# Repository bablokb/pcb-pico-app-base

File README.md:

Generic application base PCB for the Raspberry Pi Pico(W)
=========================================================

**This is work in progress**

A generic application base PCB for the Pi Pico(W) and compatible
development boards.

Core features:

  - RTC (PCF8563)
  - integrated power-management with
    - near zero power-off current
    - time-based wake up via RTC-alarm
    - wake up via interrupt (e.g. with a button)
    - JST-PH2 LiPo connector
    - LiPo charging
    - battery fuel-gauge
  - I2C connectors (Stemma/Qt and Grove)
  - EYESPI connector
  - integrated XTSD-chip for data-storage
  - additional THT for all GPIOs
  - multiple 3V3+GND connectors

License
-------

[![CC BY-SA 4.0][cc-by-sa-shield]][cc-by-sa]

This work is licensed under a
[Creative Commons Attribution-ShareAlike 4.0 International
License][cc-by-sa].

[![CC BY-SA 4.0][cc-by-sa-image]][cc-by-sa]

[cc-by-sa]: http://creativecommons.org/licenses/by-sa/4.0/
[cc-by-sa-image]: https://licensebuttons.net/l/by-sa/4.0/88x31.png
[cc-by-sa-shield]:
https://img.shields.io/badge/License-CC%20BY--SA%204.0-lightgrey.svg

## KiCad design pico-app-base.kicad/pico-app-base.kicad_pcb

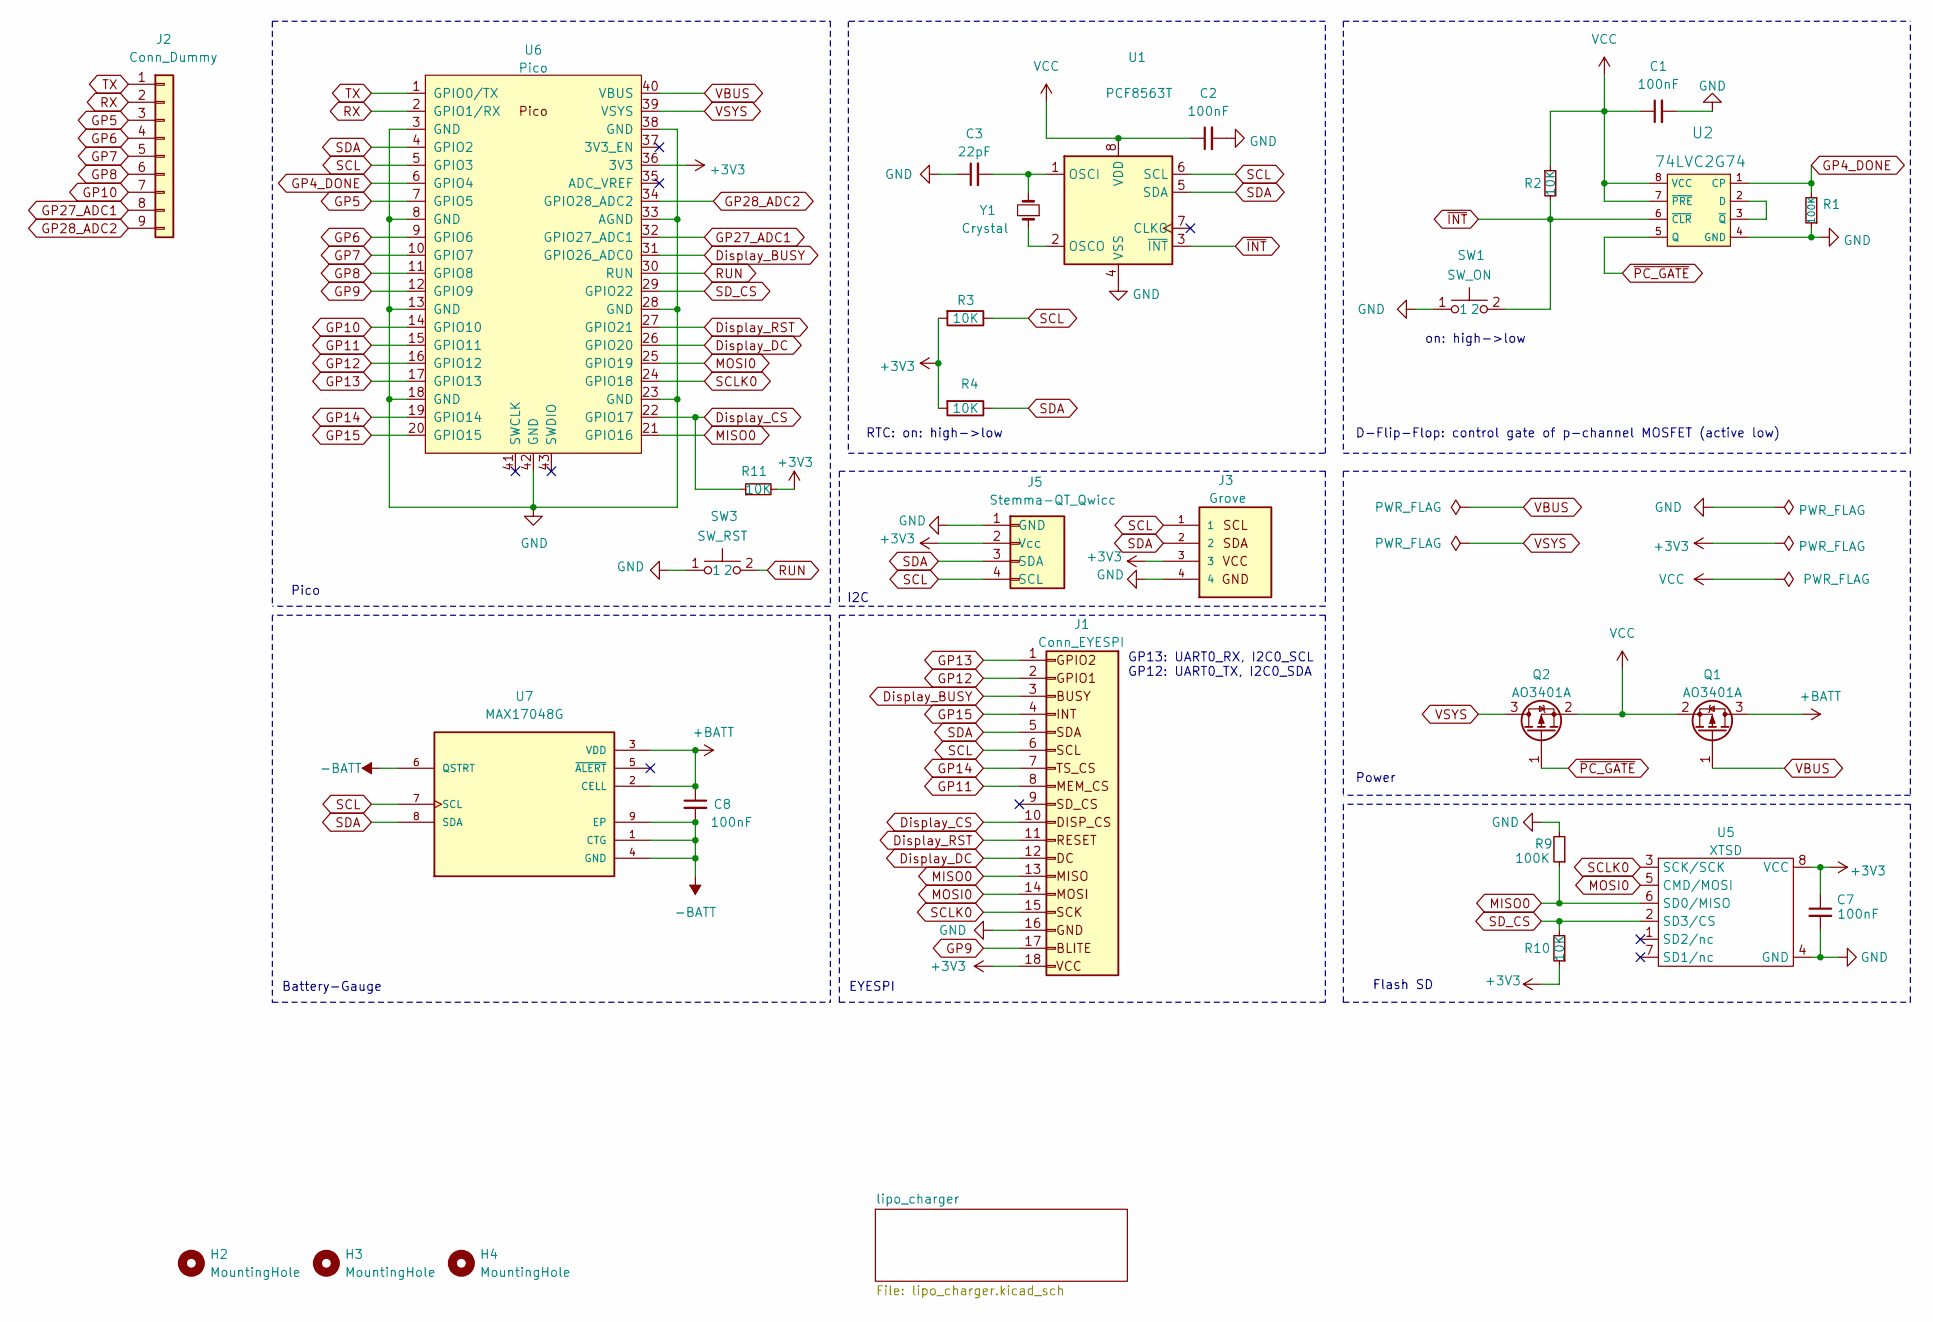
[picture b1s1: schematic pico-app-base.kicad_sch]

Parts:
C1, C2, C7, C8: 100nF; C_0402_1005Metric; LCSC C1525
C3: 22pF; C_0402_1005Metric; LCSC C1555
H2, H3, H4: MountingHole; MountingHole_2.5mm
J1: Conn_EYESPI; G-Shell-FPC_1x18_P0.50mm_Horizontal; LCSC C21260844
J2: Conn_Dummy
J3: Grove; grove_vertical
J5: Stemma-QT_Qwicc; JST_SH_SM04B-SRSS-TB_1x04-1MP_P1.00mm_Horizontal; LCSC C160404
Q1, Q2: AO3401A; SOT-23; LCSC C15127
R1, R9: 100K; R_0402_1005Metric; LCSC C25741
R2, R3, R4, R10, R11: 10K; R_0402_1005Metric; LCSC C25744
SW1: SW_ON; SW_PUSH_1x_6mm
SW3: SW_RST; SW_PUSH_1x_6mm
U1: PCF8563T; SOIC-8_3.9x4.9mm_P1.27mm; LCSC C7440
U2: 74LVC2G74; TSSOP-8_3x3mm_P0.65mm; MPN SN74HC74N; Digi-Key_PN 296-1602-5-ND
U5: XTSD; LGA8_8X6; LCSC C558837
U6: Pico; RPi_Pico_SMD_TH_extended
U7: MAX17048G; LCSC C2682616
Y1: Crystal; Crystal_SMD_3215-2Pin_3.2x1.5mm; LCSC C32346

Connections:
+3V3: C7.1, J1.18, J3.3, J5.2 (Vcc), R3.2, R4.2, R10.1, R11.2, U5.8 (VCC), U6.36 (3V3)
+BATT: C8.1, Q1.3 (D), U7.2 (CELL), U7.3 (VDD); also elsewhere on the board
-BATT: C8.2, U7.1 (CTG), U7.4 (GND), U7.6 (QSTRT), U7.9 (EP); also elsewhere on the board
Display_BUSY: J1.3, U6.31 (GPIO26_ADC0)
Display_CS: J1.10, R11.1, U6.22 (GPIO17)
Display_DC: J1.12, U6.26 (GPIO20)
Display_RST: J1.11, U6.27 (GPIO21)
GND: C1.2, C2.2, C3.1, C7.2, J1.16, J3.4, J5.1 (GND), R1.1, R9.2, SW1.1, SW3.1, U1.4 (VSS), U2.4 (GND), U5.4 (GND), U6.3 (GND), U6.8 (GND), U6.13 (GND), U6.18 (GND), U6.23 (GND), U6.28 (GND), U6.33 (AGND), U6.38 (GND), U6.42 (GND); also elsewhere on the board
GP4_DONE: R1.2, U2.1 (CP), U6.6 (GPIO4)
GP5: J2.3, U6.7 (GPIO5)
GP6: J2.4, U6.9 (GPIO6)
GP7: J2.5, U6.10 (GPIO7)
GP8: J2.6, U6.11 (GPIO8)
GP9: J1.17, U6.12 (GPIO9)
GP10: J2.7, U6.14 (GPIO10)
GP11: J1.8, U6.15 (GPIO11)
GP12: J1.2, U6.16 (GPIO12)
GP13: J1.1, U6.17 (GPIO13)
GP14: J1.7, U6.19 (GPIO14)
GP15: J1.4, U6.20 (GPIO15)
GP27_ADC1: J2.8, U6.32 (GPIO27_ADC1)
GP28_ADC2: J2.9, U6.34 (GPIO28_ADC2)
MISO0: J1.13, R9.1, U5.6 (SD0/MISO), U6.21 (GPIO16)
MOSI0: J1.14, U5.5 (CMD/MOSI), U6.25 (GPIO19)
unnamed: C3.2, U1.1 (OSCI), Y1.2
unnamed: U1.2 (OSCO), Y1.1
unnamed: U2.2 (D), U2.3 (~Q)
RUN: SW3.2, U6.30 (RUN)
RX: J2.2, U6.2 (GPIO1/RX)
SCL: J1.6, J3.1, J5.4 (SCL), R3.1, U1.6 (SCL), U6.5 (GPIO3), U7.7 (SCL)
SCLK0: J1.15, U5.3 (SCK/SCK), U6.24 (GPIO18)
SDA: J1.5, J3.2, J5.3 (SDA), R4.1, U1.5 (SDA), U6.4 (GPIO2), U7.8 (SDA)
SD_CS: R10.2, U5.2 (SD3/CS), U6.29 (GPIO22)
TX: J2.1, U6.1 (GPIO0/TX)
VBUS: Q1.1 (G), U6.40 (VBUS); also elsewhere on the board
VCC: C1.1, C2.1, Q1.2 (S), Q2.2 (S), R2.1, U1.8 (VDD), U2.7 (~PRE), U2.8 (VCC)
VSYS: Q2.3 (D), U6.39 (VSYS)
~INT: R2.2, SW1.2, U1.3 (~INT), U2.6 (~CLR)
~PC_GATE: Q2.1 (G), U2.5 (Q)

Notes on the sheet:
Battery-Gauge
EYESPI
Power
Flash SD
D-Flip-Flop: control gate of p-channel MOSFET (active low)
Pico
RTC: on: high->low
I2C
on: high->low
GP13: UART0_RX, I2C0_SCL GP12: UART0_TX, I2C0_SDA

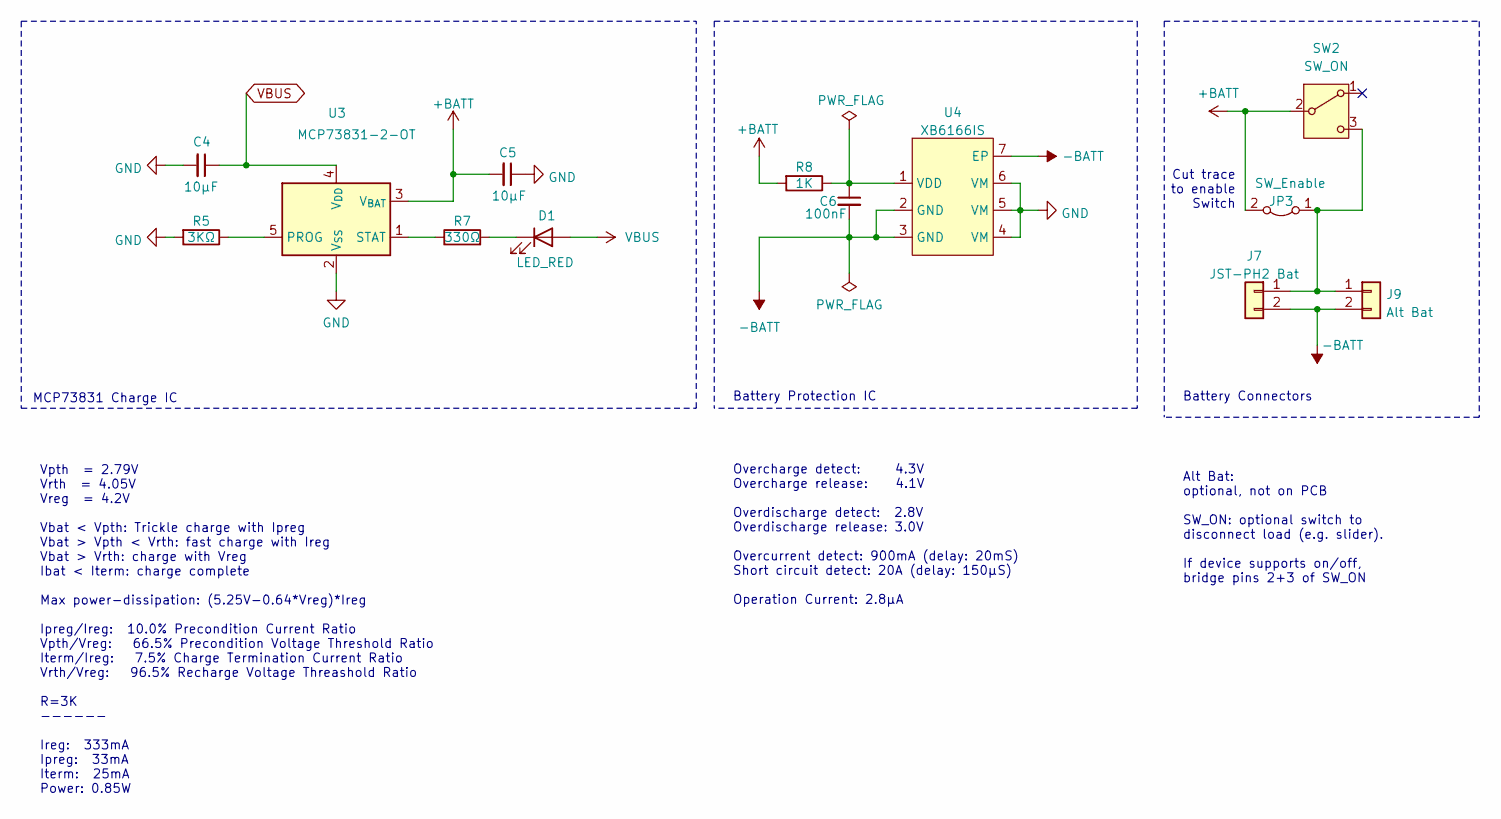
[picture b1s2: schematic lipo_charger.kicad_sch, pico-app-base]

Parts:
C4, C5: 10µF; C_0603_1608Metric; LCSC C19702
C6: 100nF; C_0402_1005Metric; LCSC C1525
D1: LED_RED; LED_0805_2012Metric; LCSC C84256
J7: JST-PH2 Bat; JST_PH_S2B-PH-SM4-TB_1x02-1MP_P2.00mm_Horizontal; LCSC C295747
J9: Alt Bat; PinHeader_1x02_P2.54mm_Vertical
JP3: SW_Enable; SolderJumper-2_P1.3mm_Bridged_Pad1.0x1.5mm
R5: 3KΩ; R_0603_1608Metric; LCSC C4211
R7: 330Ω; R_0402_1005Metric; LCSC C25104
R8: 1K; R_0603_1608Metric; LCSC C21190
SW2: SW_ON; PinHeader_1x03_P2.54mm_Vertical
U3: MCP73831-2-OT; SOT-23-5; LCSC C424093
U4: XB6166IS; DFN-2x2mm-0.75; LCSC C94310

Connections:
+BATT: C5.2, JP3.2 (B), R8.2, SW2.2 (B), U3.3 (V_{BAT}); also elsewhere on the board
-BATT: C6.2, J7.2, J9.2, U4.2 (GND), U4.3 (GND), U4.7 (EP); also elsewhere on the board
GND: C4.2, C5.1, R5.2, U3.2 (V_{SS}), U4.4 (VM), U4.5 (VM), U4.6 (VM); also elsewhere on the board
unnamed: D1.1 (K), R7.2
unnamed: J7.1, J9.1, JP3.1 (A), SW2.3 (C)
unnamed: R5.1, U3.5 (PROG)
unnamed: R7.1, U3.1 (STAT)
unnamed: C6.1, R8.1, U4.1 (VDD)
VBUS: C4.1, D1.2 (A), U3.4 (V_{DD}); also elsewhere on the board

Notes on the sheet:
Alt Bat: optional, not on PCB SW_ON: optional switch to disconnect load (e.g. slider). If device supports on/off, bridge pins 2+3 of SW_ON
Battery Connectors
MCP73831 Charge IC
Vpth = 2.79V Vrth = 4.05V Vreg = 4.2V Vbat < Vpth: Trickle charge with Ipreg Vbat > Vpth < Vrth: fast charge with Ireg Vbat > Vrth: charge with Vreg Ibat < Iterm: charge complete Max power-dissipation: (5.25V-0.64*Vreg)*Ireg Ipreg/Ireg: 10.0% Precondition Current Ratio Vpth/Vreg: 66.5% Precondition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
Battery Protection IC
Overcharge detect: 4.3V Overcharge release: 4.1V Overdischarge detect: 2.8V Overdischarge release: 3.0V Overcurrent detect: 900mA (delay: 20mS) Short circuit detect: 20A (delay: 150µS) Operation Current: 2.8µA
Cut trace to enable Switch

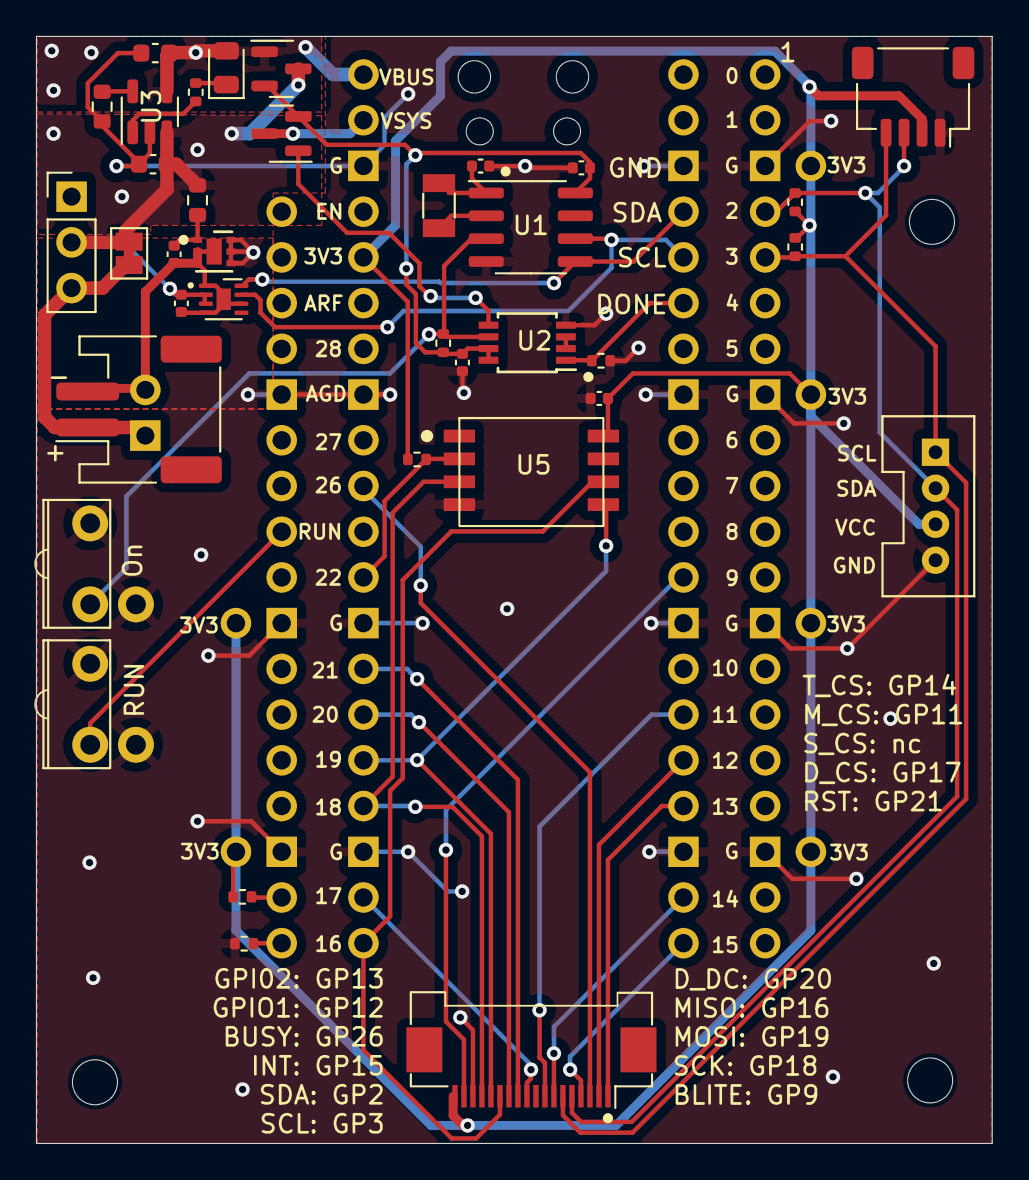
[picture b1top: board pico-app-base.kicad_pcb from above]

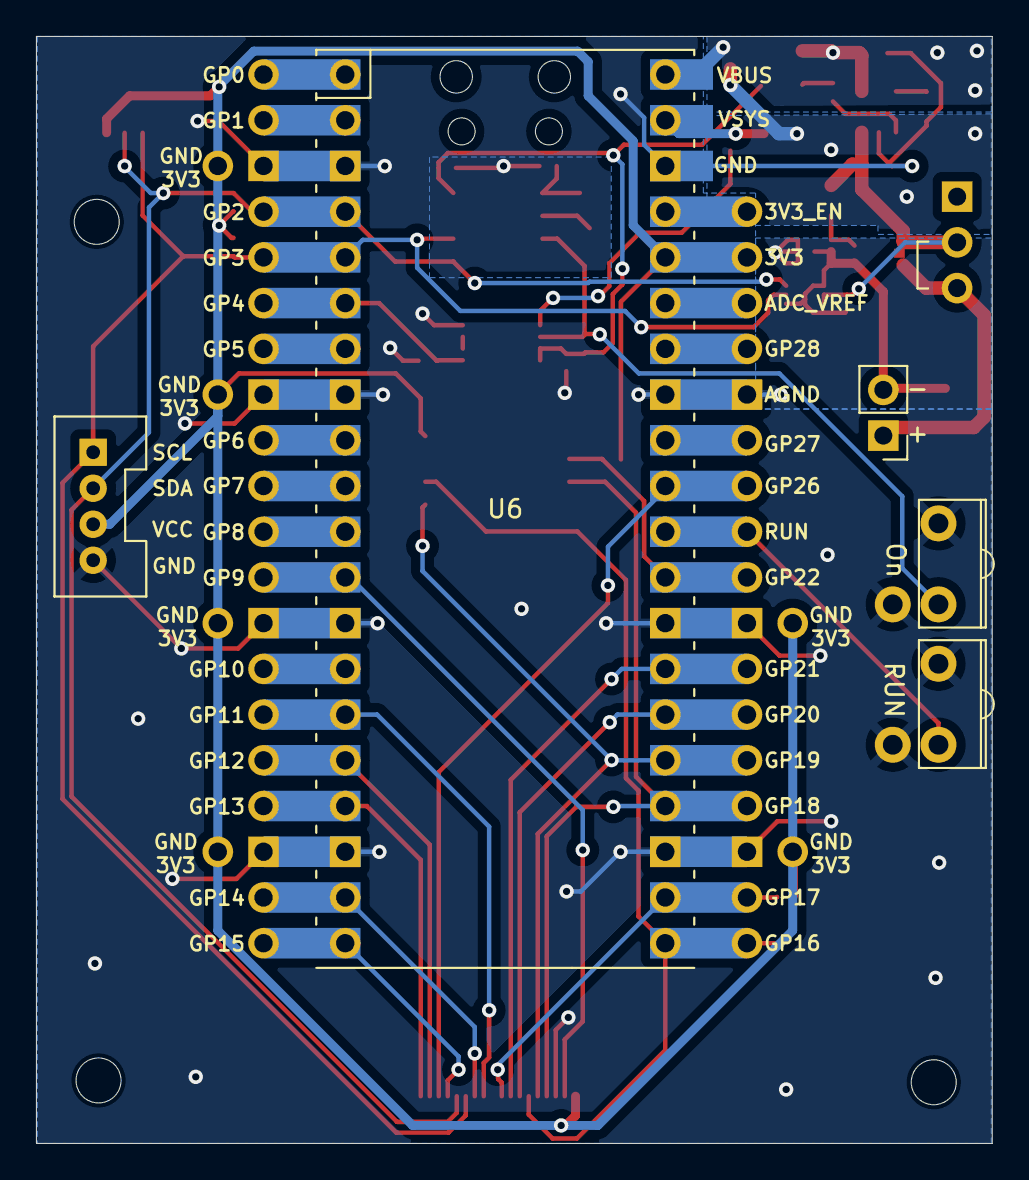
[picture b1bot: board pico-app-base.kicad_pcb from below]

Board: 2 copper layers, 53.1 x 61.5 mm, 41 parts (2 on the bottom side), 35 nets.

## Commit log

2024-05-16 initial project setup
2024-05-16 preliminary version
2024-05-28 added zones and connections
2024-06-10 added *.lck
2024-06-10 switched order of mosfets
2024-06-20 added I2C-grove, completed routing
2024-06-25 document pin usage
2024-06-25 added labels
2024-08-09 added battery-fuel gauge
2024-08-09 added project description
